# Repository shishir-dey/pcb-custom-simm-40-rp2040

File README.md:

# pcb-custom-simm-40-rp2040

Reference: [Raspberry Pi Pico Datasheet](Docs/pico-datasheet.pdf)

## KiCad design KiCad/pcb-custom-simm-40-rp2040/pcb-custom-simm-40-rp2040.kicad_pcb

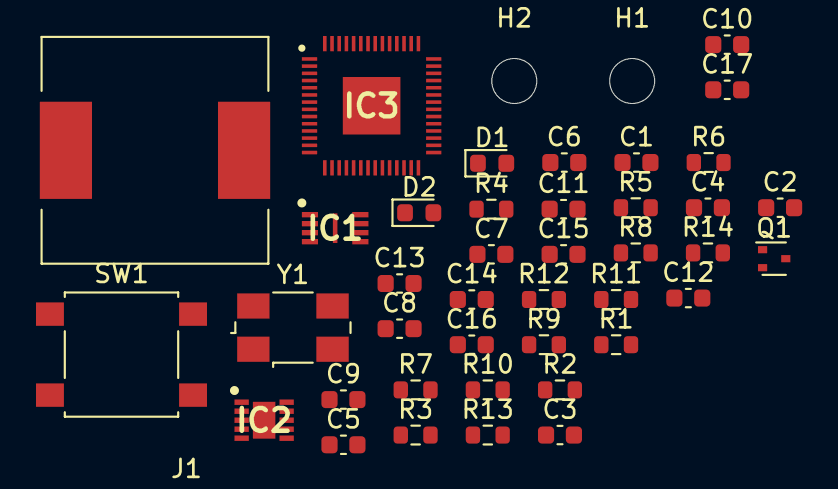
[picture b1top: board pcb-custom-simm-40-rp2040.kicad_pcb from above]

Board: 2 copper layers, 43 parts (0 on the bottom side), 26 nets, no tracks yet.

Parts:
C1: 1n; C_0603_1608Metric
C2, C3: 47u; C_0603_1608Metric
C4, C6: 15pf; C_0603_1608Metric
C5: 2u2, 6.3V; C_0603_1608Metric
C7: 100n, 6.3V; C_0603_1608Metric
C8, C9, C10, C11, C12, C14, C15, C16: 100n; C_0603_1608Metric
C13, C17: 2u2; C_0603_1608Metric
D1: MBR120VLSFT1G; D_0603_1608Metric
D2: GREEN_LED; LED_0603_1608Metric
H1, H2: MountingHole; MountingHole_2.5mm
IC1: W25Q16JVUXIQ_TR; SON50P300X200X60-9N
IC2: RT6150B-33GQW; SON50P250X250X80-11N-D
IC3: RP2040; QFN40P700X700X90-57N-D
J1: SIMM-40 Connector; MySIMM_40
L1: 2u2; L_12x12mm_H4.5mm
Q1: DMG1012T; SOT-523
R1: 5K8; R_0603_1608Metric
R2: 10K; R_0603_1608Metric
R3, R7: DNL; R_0603_1608Metric
R4: 200K; R_0603_1608Metric
R5, R6, R9: 100K; R_0603_1608Metric
R8: 1K; R_0603_1608Metric
R10: 470E; R_0603_1608Metric
R11, R12: 27R; R_0603_1608Metric
R13: 200R; R_0603_1608Metric
R14: 1R; R_0603_1608Metric
SW1: SW_Push_Dual; SW_SPST_B3S-1000
Y1: 12MHz; Crystal_SMD_0603-4Pin_6.0x3.5mm

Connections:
3V3_EN: IC2.6, R6.2
+1V1: C9.1, C11.1, C13.1, IC3.23, IC3.45, IC3.50
+3V3: C3.1, C5.1, C7.1, C8.1, C10.1, C12.1, C14.1, C15.1, C16.1, C17.1, IC1.8, IC2.1, IC2.10, IC3.1, IC3.10, IC3.22, IC3.33, IC3.42, IC3.44, IC3.48, IC3.49, Q1.1, R3.2, R13.1
+5V: D1.2, R1.1
ADC_VREF: R13.2, R14.1
GND: C1.2, C2.2, C3.2, C4.2, C5.2, C6.2, C7.2, C9.2, C11.2, C13.2, D2.1, IC1.4, IC2.3, IC2.9, IC2.11, IC3.19, IC3.43, IC3.57, R2.2, R5.2, R9.2, R14.2, Y1.2, Y1.4
GPIO23: IC2.7, IC3.35, R9.1
GPIO24: IC3.36, R1.2, R2.1
GPIO25: IC3.37, R10.2
GPIO29: IC3.41, Q1.2
unnamed: C1.1, Q1.3, R4.2, R5.1
unnamed: C8.2, C10.2, C12.2, C14.2, C15.2, C16.2, C17.2
unnamed: D2.2, R10.1
unnamed: IC2.2, L1.2
unnamed: IC2.4, L1.1
unnamed: IC3.46, R12.2
unnamed: IC3.47, R11.2
unnamed: R8.1, SW1.1, SW1.2
QSPI_SD0: IC1.5, IC3.53
QSPI_SD1: IC1.2, IC3.55
QSPI_SD2: IC1.3, IC3.54
QSPI_SD3: IC1.7, IC3.51
QSPI_SS: IC1.1, IC3.56, R3.1, R8.2
VIN: C2.1, D1.1, IC2.5, IC2.8, R4.1, R6.1
XIN: C4.1, IC3.20, R7.2, Y1.1
XOUT: C6.1, IC3.21, R7.1, Y1.3

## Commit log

2021-11-15 Create LICENSE
2021-11-15 Add KiCad project with schematics
2021-11-15 Create custom SIMM-40 footprint
2021-11-15 Add custom footprint to project. Update schematics, layout and documents
2021-11-19 Add Raspberry Pi Pico Datasheet
